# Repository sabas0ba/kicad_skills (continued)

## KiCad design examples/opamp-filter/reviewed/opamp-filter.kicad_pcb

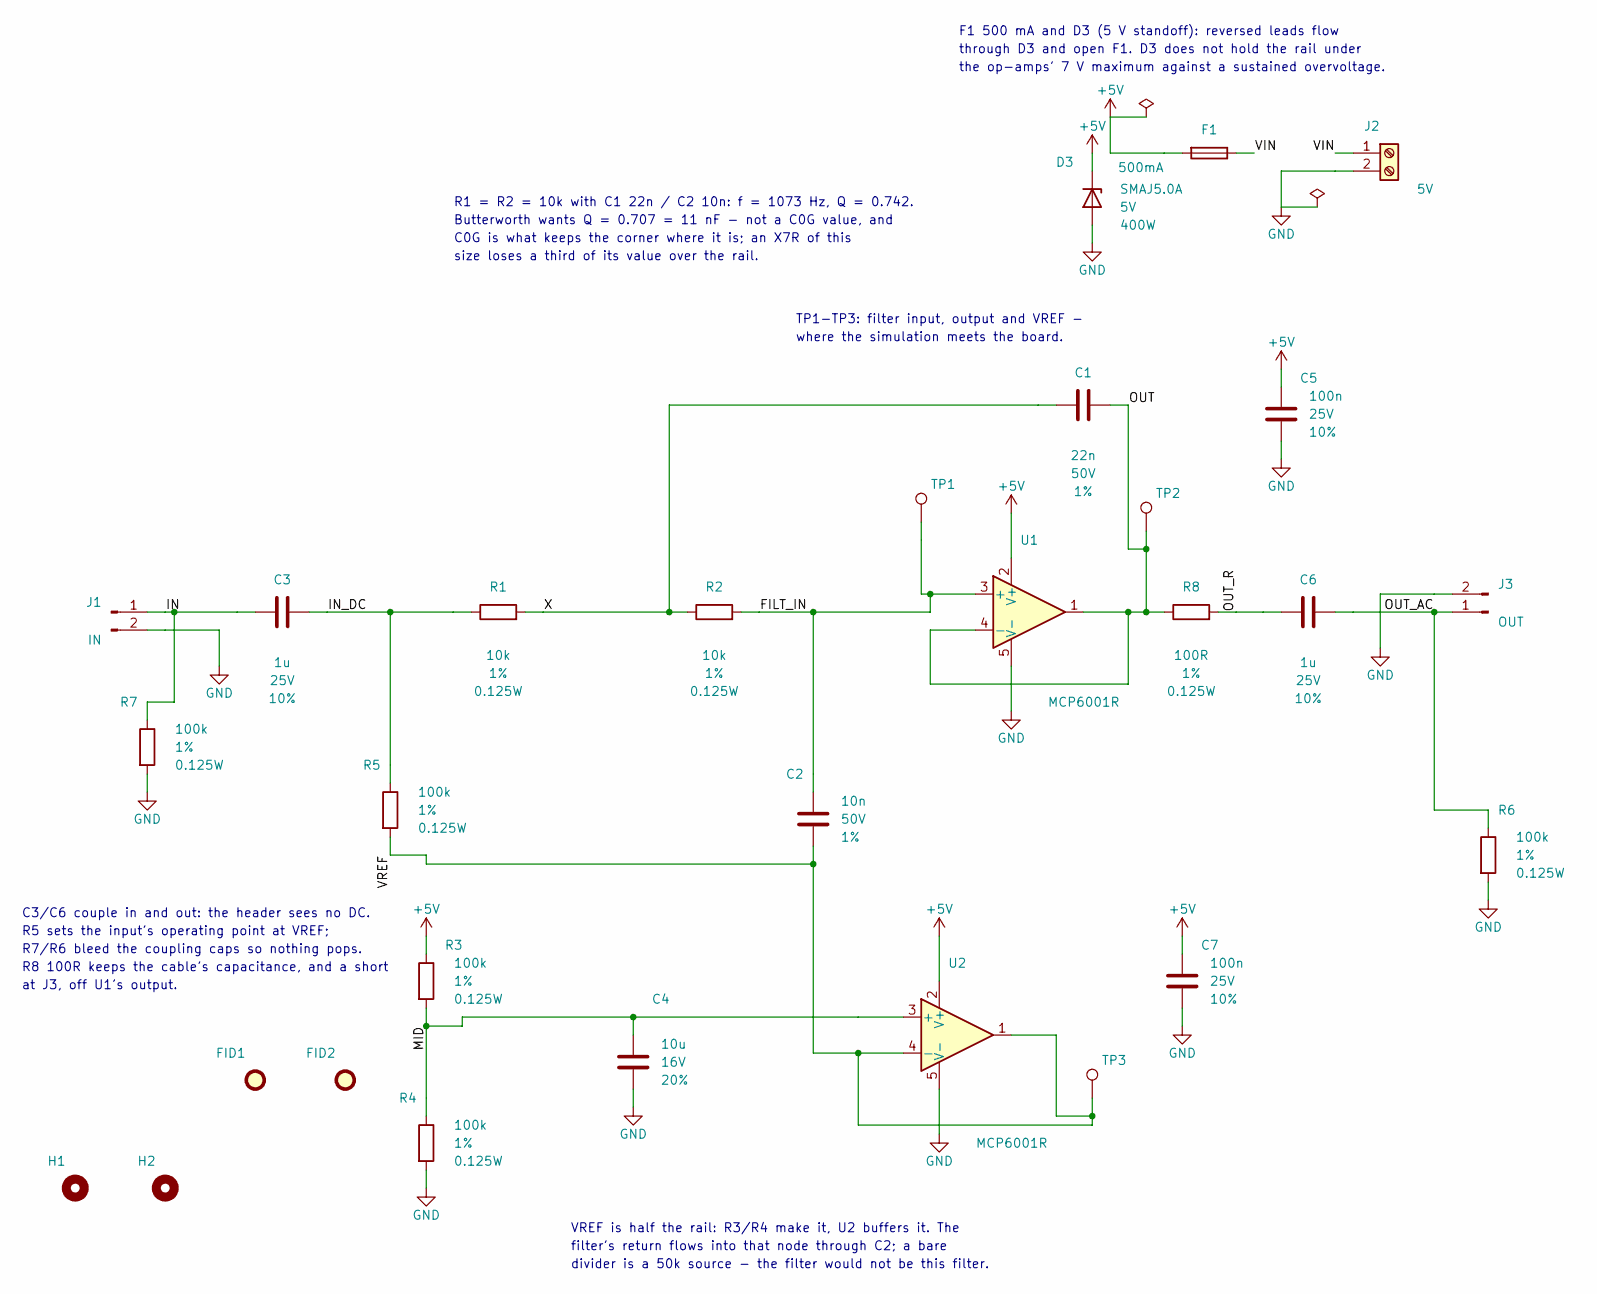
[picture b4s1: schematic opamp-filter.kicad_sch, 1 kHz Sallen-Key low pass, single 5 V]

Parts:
C1: 22n; C_0805_2012Metric; Voltage 50V; Tolerance 1%; MPN CL21C223JBFNNNE
C2: 10n; C_0805_2012Metric; Voltage 50V; Tolerance 1%; MPN CL21C103JBFNNNE
C3, C6: 1u; C_0805_2012Metric; Voltage 25V; Tolerance 10%; MPN CL21B105KBFNNNE
C4: 10u; C_0805_2012Metric; Voltage 16V; Tolerance 20%; MPN CL21A106KOQNNNE
C5, C7: 100n; C_0805_2012Metric; Voltage 25V; Tolerance 10%; MPN CL21B104KBCNNNC
D3: SMAJ5.0A; D_SMA; Voltage 5V; MPN SMAJ5.0A
F1: 500mA; Fuse_1206_3216Metric; MPN 0466.500NR
FID1, FID2: Fiducial; Fiducial_1mm_Mask2mm; MPN n/a
H1, H2: M3; MountingHole_3.2mm_M3; MPN n/a
J1: IN; PinHeader_1x02_P2.54mm_Vertical; MPN 61300211121
J2: 5V; TerminalBlock_Phoenix_MKDS-1,5-2_1x02_P5.00mm_Horizontal; MPN 1729128
J3: OUT; PinHeader_1x02_P2.54mm_Vertical; MPN 61300211121
R1, R2: 10k; R_0805_2012Metric; Tolerance 1%; MPN RC0805FR-0710KL
R3, R4, R5, R6, R7: 100k; R_0805_2012Metric; Tolerance 1%; MPN RC0805FR-07100KL
R8: 100R; R_0805_2012Metric; Tolerance 1%; MPN RC0805FR-07100RL
TP1, TP2, TP3: TP; TestPoint_Pad_D1.5mm
U1, U2: MCP6001R; SOT-23-5; MPN MCP6001RT-I/OT

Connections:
+5V: C5.1, C7.1, D3.1 (K), F1.2, R3.1, U1.2 (V+), U2.2 (V+)
/FILT_IN: C2.1, R2.2, TP1.1, U1.3 (+)
/IN: C3.1, J1.1, R7.1
/IN_DC: C3.2, R1.1, R5.1
/MID: C4.1, R3.2, R4.1, U2.3 (+)
/OUT: C1.2, R8.1, TP2.1, U1.1, U1.4 (-)
/OUT_AC: C6.2, J3.1, R6.1
/OUT_R: C6.1, R8.2
/VIN: F1.1, J2.1
/VREF: C2.2, R5.2, TP3.1, U2.1, U2.4 (-)
/X: C1.1, R1.2, R2.1
GND: C4.2, C5.2, C7.2, D3.2 (A), J1.2, J2.2, J3.2, R4.2, R6.2, R7.2, U1.5 (V-), U2.5 (V-)

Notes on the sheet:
R1 = R2 = 10k with C1 22n / C2 10n: f = 1073 Hz, Q = 0.742.
Butterworth wants Q = 0.707 = 11 nF - not a C0G value, and
C0G is what keeps the corner where it is; an X7R of this
size loses a third of its value over the rail.
VREF is half the rail: R3/R4 make it, U2 buffers it. The
filter's return flows into that node through C2; a bare
divider is a 50k source - the filter would not be this filter.
C3/C6 couple in and out: the header sees no DC.
R5 sets the input's operating point at VREF;
R7/R6 bleed the coupling caps so nothing pops.
R8 100R keeps the cable's capacitance, and a short
at J3, off U1's output.
F1 500 mA and D3 (5 V standoff): reversed leads flow
through D3 and open F1. D3 does not hold the rail under
the op-amps' 7 V maximum against a sustained overvoltage.
TP1-TP3: filter input, output and VREF -
where the simulation meets the board.

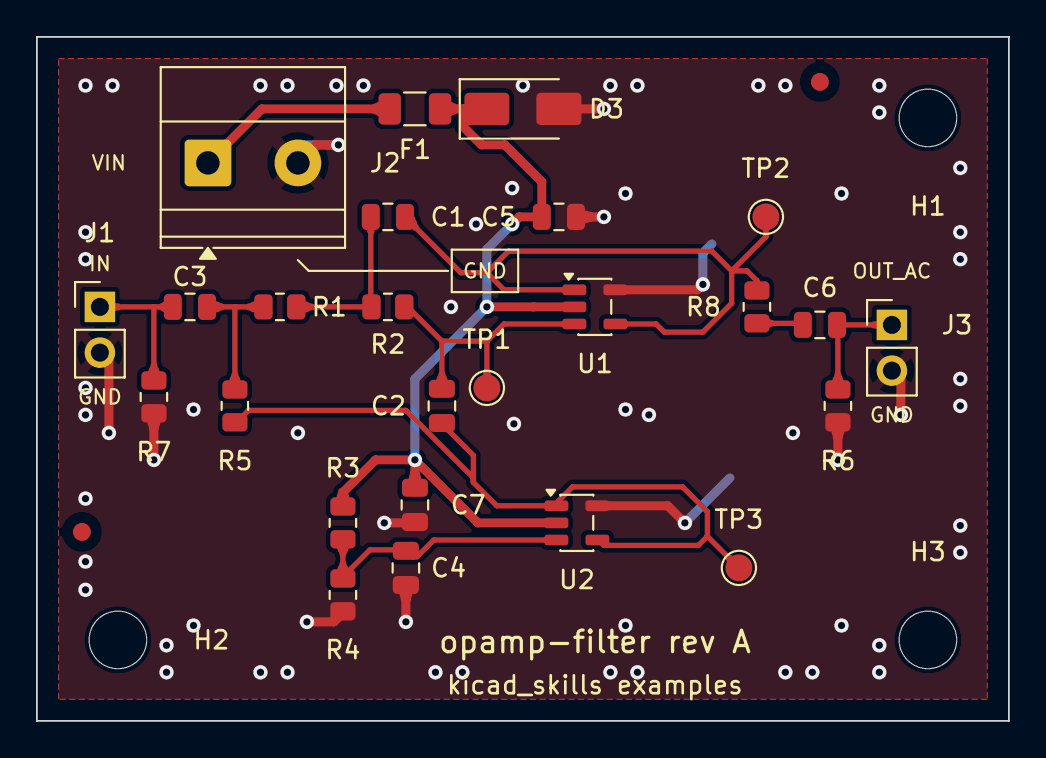
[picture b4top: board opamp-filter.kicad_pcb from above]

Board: 2 copper layers, 54.0 x 38.0 mm, 30 parts (0 on the bottom side), 12 nets.

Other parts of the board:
H3: M3; MountingHole_3.2mm_M3

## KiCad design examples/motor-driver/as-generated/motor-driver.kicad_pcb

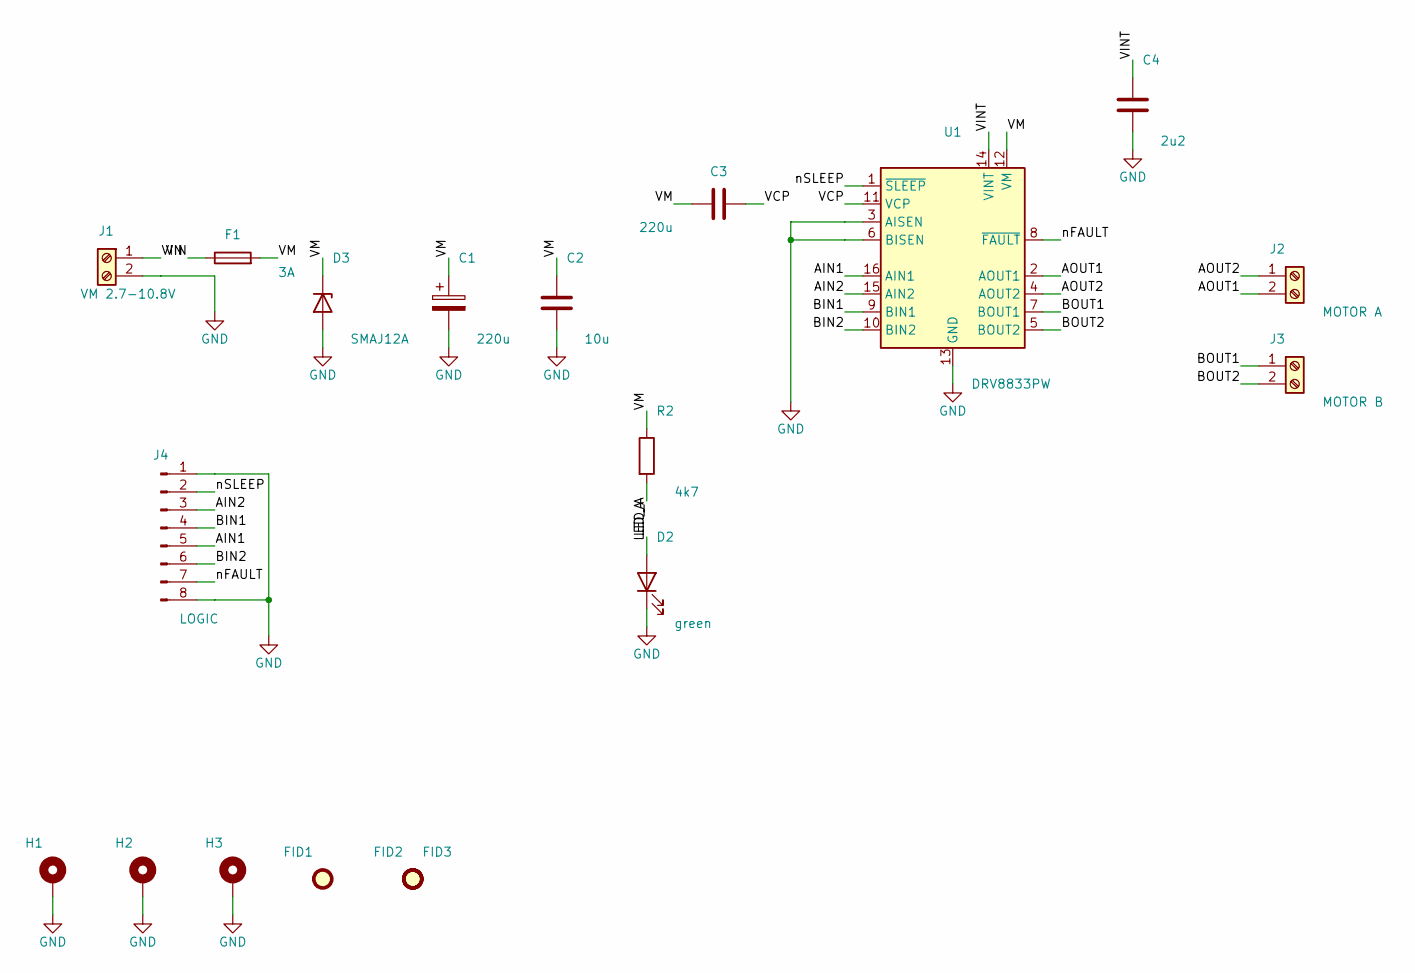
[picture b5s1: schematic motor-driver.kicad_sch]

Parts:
C1: 220u; CP_Elec_6.3x7.7
C2: 10u; C_0805_2012Metric
C3: 220u; C_0805_2012Metric
C4: 2u2; C_0805_2012Metric
D2: green; LED_0805_2012Metric
D3: SMAJ12A; D_SMA
F1: 3A; Fuse_1206_3216Metric
FID1, FID2, FID3: Fiducial; Fiducial_1mm_Mask2mm
H1, H2, H3: M3; MountingHole_3.2mm_M3_Pad
J1: VM 2.7-10.8V; TerminalBlock_Phoenix_MKDS-1,5-2_1x02_P5.00mm_Horizontal
J2: MOTOR A; TerminalBlock_Phoenix_MKDS-1,5-2_1x02_P5.00mm_Horizontal
J3: MOTOR B; TerminalBlock_Phoenix_MKDS-1,5-2_1x02_P5.00mm_Horizontal
J4: LOGIC; PinHeader_1x08_P2.54mm_Vertical
R2: 4k7; R_0805_2012Metric
U1: DRV8833PW; TSSOP-16_4.4x5mm_P0.65mm

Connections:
/AIN1: J4.5, U1.16 (AIN1)
/AIN2: J4.3, U1.15 (AIN2)
/AOUT1: J2.2, U1.2 (AOUT1)
/AOUT2: J2.1, U1.4 (AOUT2)
/BIN1: J4.4, U1.9 (BIN1)
/BIN2: J4.6, U1.10 (BIN2)
/BOUT1: J3.1, U1.7 (BOUT1)
/BOUT2: J3.2, U1.5 (BOUT2)
/LED_A: D2.2 (A), R2.2
/VCP: C3.2, U1.11 (VCP)
/VIN: F1.1, J1.1
/VINT: C4.1, U1.14 (VINT)
/VM: C1.1, C2.1, C3.1, D3.1 (K), F1.2, R2.1, U1.12 (VM)
/nFAULT: J4.7, U1.8 (~FAULT)
/nSLEEP: J4.2, U1.1 (~SLEEP)
GND: C1.2, C2.2, C4.2, D2.1 (K), D3.2 (A), H1.1, H2.1, H3.1, J1.2, J4.1, J4.8, U1.3 (AISEN), U1.6 (BISEN), U1.13 (GND)

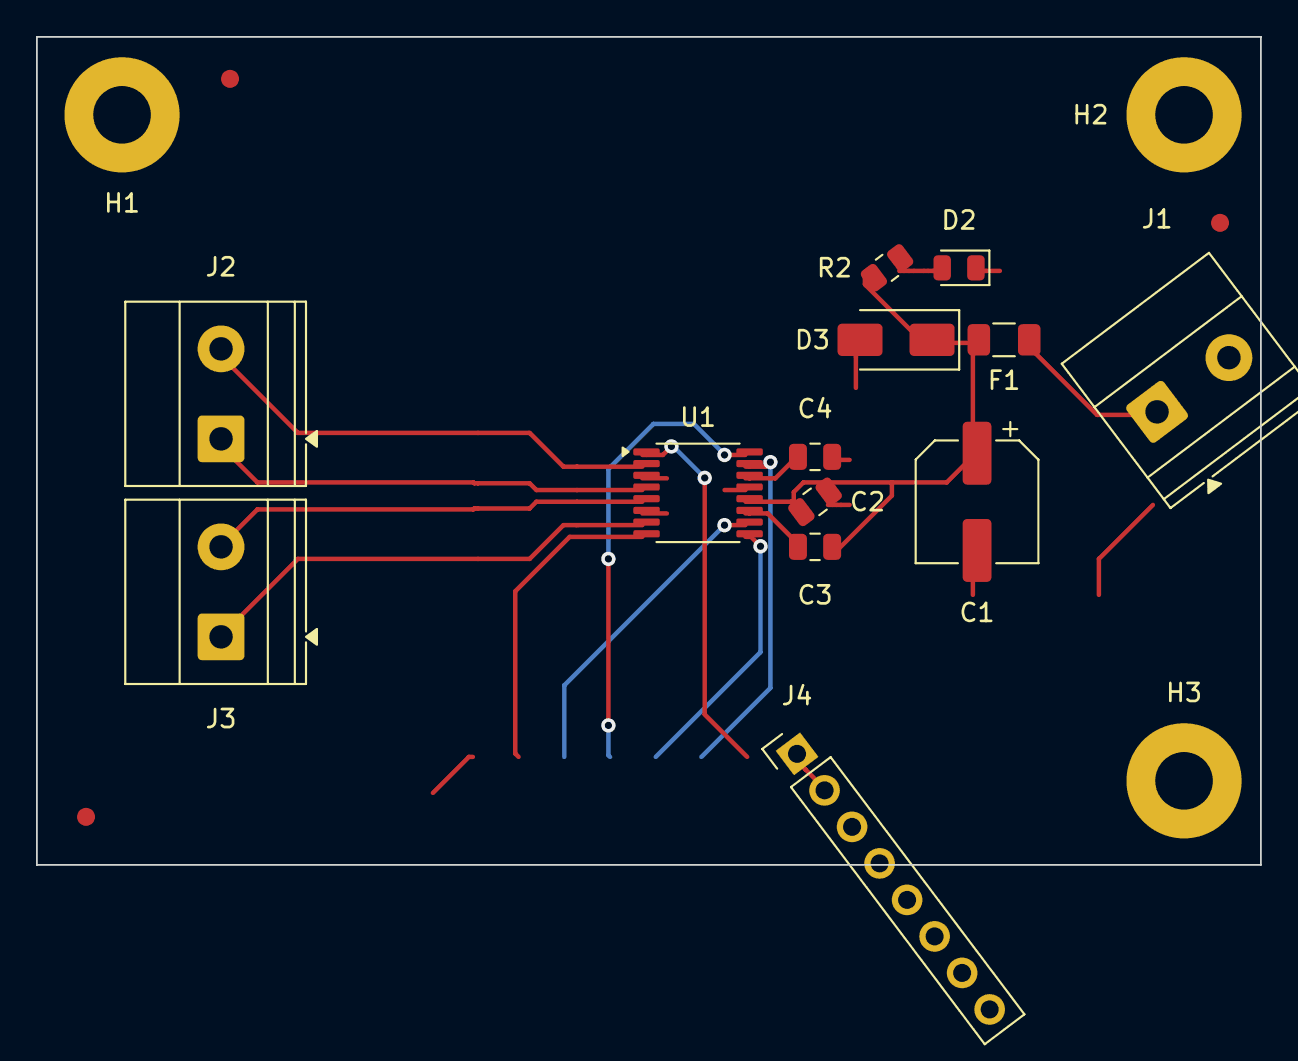
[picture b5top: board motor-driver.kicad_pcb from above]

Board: 2 copper layers, 68.0 x 46.0 mm, 19 parts (0 on the bottom side), 16 nets.

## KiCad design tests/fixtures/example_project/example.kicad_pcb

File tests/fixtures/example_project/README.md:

# Example project

A tiny but complete KiCad project used by the test-suite and by the skill
documentation: a passive RC low pass (R1/C1, fc ≈ 1.6 kHz) followed by an LM321
unity gain buffer, with a local decoupling capacitor (C2) and a 3-pin connector.

* `example.kicad_sch` — schematic. The symbols are the real ones from the KiCad
  standard libraries, embedded in `lib_symbols` as KiCad itself does. It is
  written in the **oldest format the CI matrix covers**, with no KiCad 10 only
  tokens (`duplicate_pin_numbers_are_jumpers`, `in_pos_files`, `(power global)`),
  because KiCad never reads a file newer than itself — one such token and
  KiCad 9 refuses the whole document.
* `example.kicad_pcb` — 40 × 30 mm two layer board, routed, with a **filled**
  ground pour on `B.Cu` (saved by KiCad 9's pcbnew, so both matrix versions read
  it). The fill is committed on purpose: KiCad 9's `pcb drc` has no
  `--refill-zones`, so an unfilled pour there means GND reads as unconnected —
  which is exactly what a real project would suffer. The footprints are
  **simplified copies** of the standard ones (pads and reference text only), so
  DRC reports a `lib_footprint_mismatch` warning for each of them. That is
  expected: it keeps the fixture small and readable while still exercising every
  code path.
* `example.kicad_pro` — project settings (net classes, design rules).

The board is DRC clean apart from those library mismatches, so a new error in
`eda pcb review tests/fixtures/example_project` means the toolkit changed
behaviour, not that the board is broken.

The schematic is also **fully specified**, and deliberately so: R1 carries a
tolerance and a power rating, both capacitors carry a voltage rating and a
tolerance, J1 and U1 carry manufacturer part numbers, and a text note records
why the values are what they are. That is what makes
`eda gate tests/fixtures/example_project --policy ai-generated` pass, and it is
the reference for what the `spec.*` rules ask of a design. Stripping any of it
turns the fixture into an example of the thing those rules exist to catch.

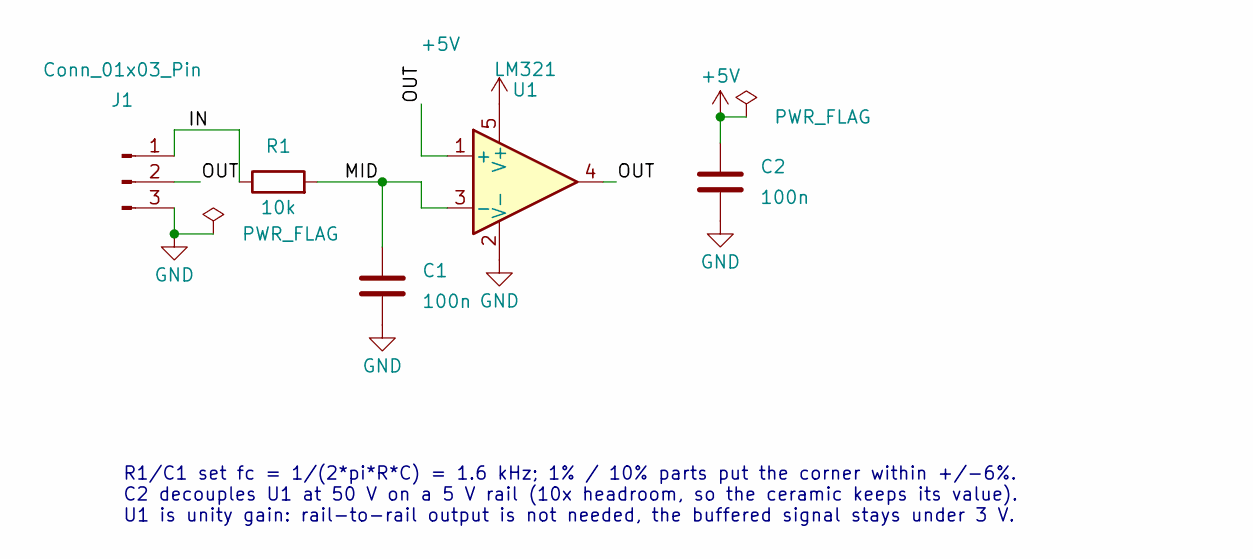
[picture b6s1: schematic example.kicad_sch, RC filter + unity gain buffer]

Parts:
C1, C2: 100n; C_0805_2012Metric; Voltage 50V; Tolerance 10%
J1: Conn_01x03_Pin; PinHeader_1x03_P2.54mm_Vertical; MPN 61300311121
R1: 10k; R_0805_2012Metric; Tolerance 1%
U1: LM321; SOT-23-5; MPN LM321MF/NOPB

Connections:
+5V: C2.1, U1.5 (V+)
/IN: J1.1, R1.1
/MID: C1.1, R1.2, U1.3 (-)
/OUT: J1.2, U1.1 (+), U1.4
GND: C1.2, C2.2, J1.3, U1.2 (V-)

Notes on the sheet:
R1/C1 set fc = 1/(2*pi*R*C) = 1.6 kHz; 1% / 10% parts put the corner within +/-6%. C2 decouples U1 at 50 V on a 5 V rail (10x headroom, so the ceramic keeps its value). U1 is unity gain: rail-to-rail output is not needed, the buffered signal stays under 3 V.

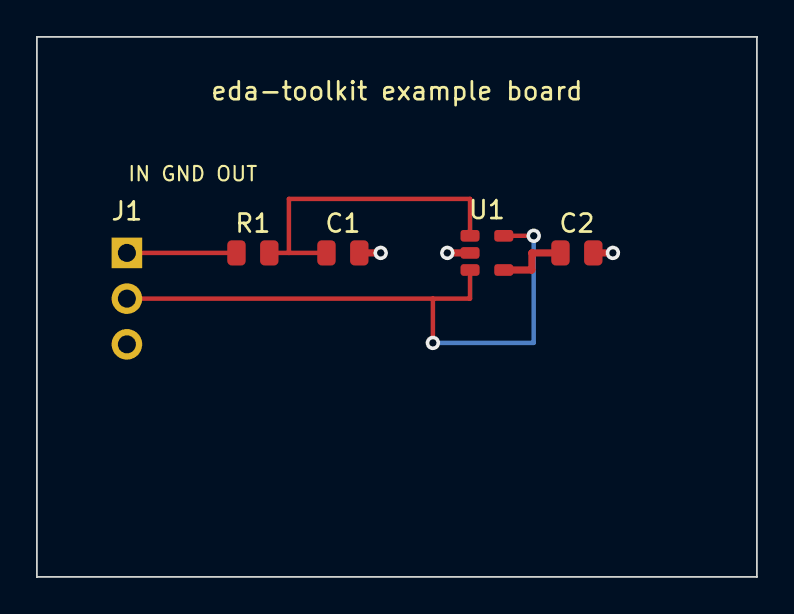
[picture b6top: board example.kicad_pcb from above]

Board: 2 copper layers, 40.0 x 30.0 mm, 5 parts (0 on the bottom side), 5 nets.
